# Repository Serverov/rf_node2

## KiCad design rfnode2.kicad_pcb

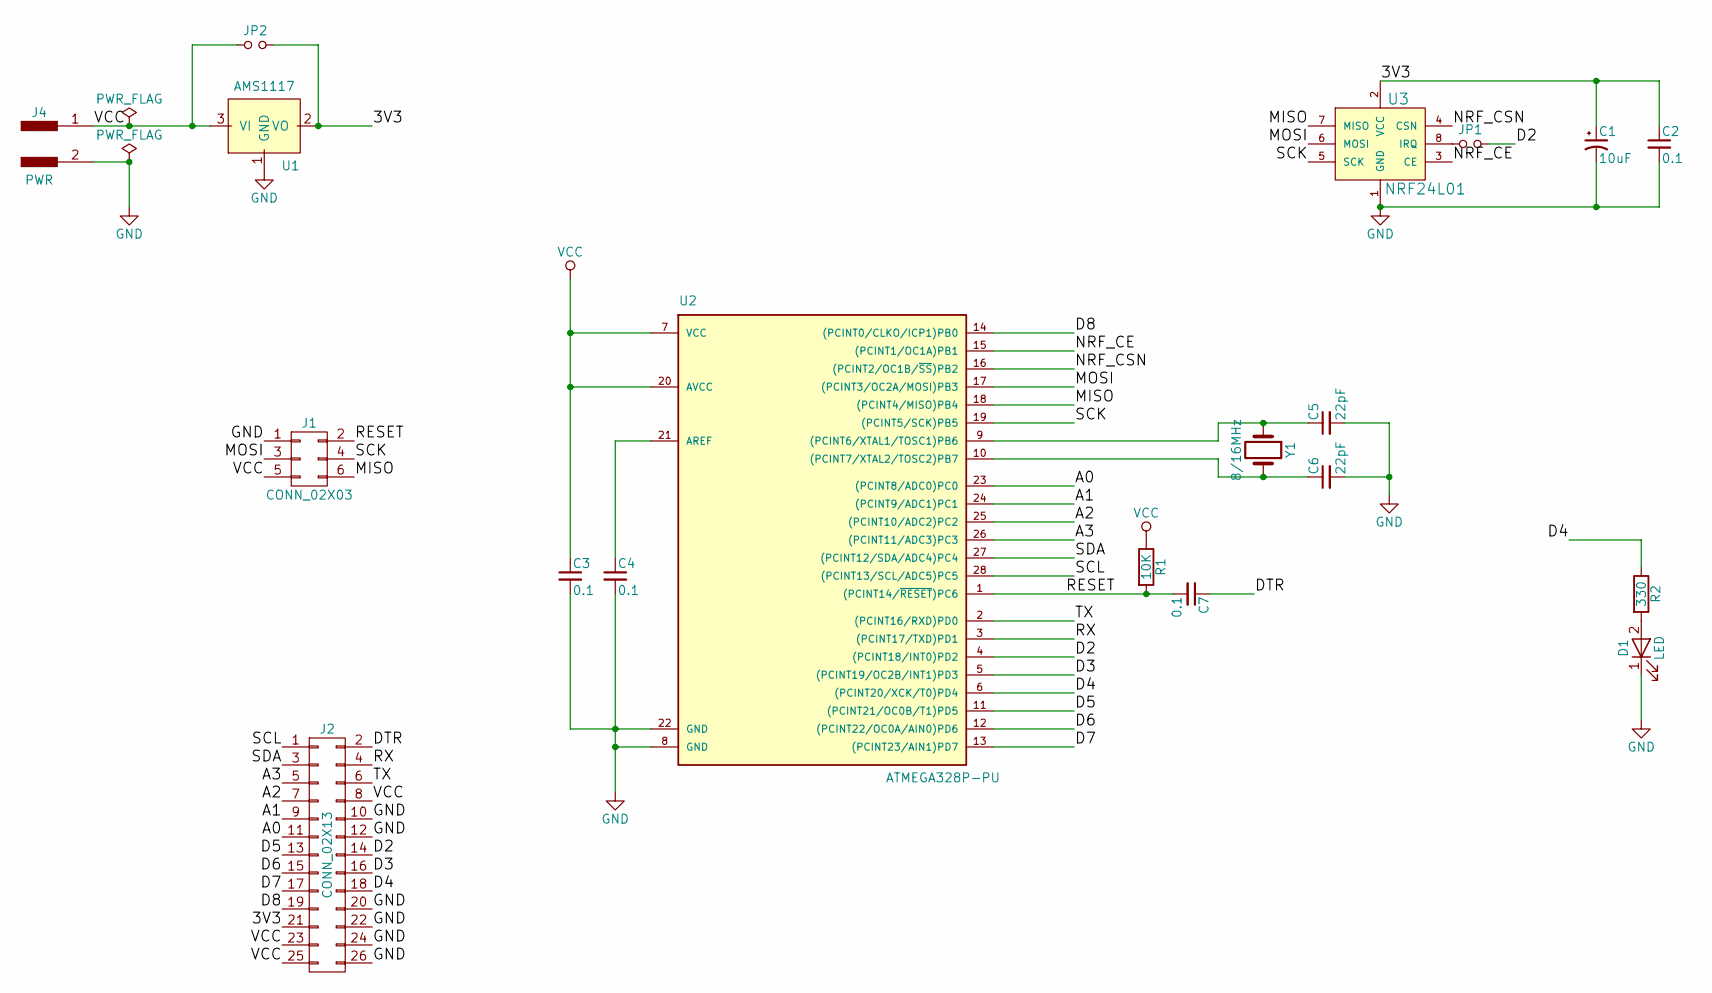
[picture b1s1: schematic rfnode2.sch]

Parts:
C1: 10uF; CP_Radial_D5.0mm_P2.00mm
C2, C3, C4, C7: 0.1; C_0805_HandSoldering
C5, C6: 22pF; C_0805_HandSoldering
D1: LED; LED_D3.0mm
J1: CONN_02X03; Pin_Header_Straight_2x03_Pitch2.54mm
J2: CONN_02X13; Pin_Header_Straight_2x13_Pitch2.54mm
J4: PWR; Pin_Header_Straight_1x02_Pitch2.54mm
JP1: IRQ; S_JUMPER_2
JP2: 3V3; S_JUMPER_2
R1: 10K; R_0805_HandSoldering
R2: 330; R_0805_HandSoldering
U1: AMS1117; SOT-223
U2: ATMEGA328P-PU; DIP-28_W7.62mm_Socket
U3: NRF24L01
Y1: 8/16MHz; Resonator-2pin_w10.0mm_h5.0mm

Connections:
/3V3: C1.1, C2.1, J2.21, JP2.2, U1.2 (VO), U3.2 (VCC)
/A0: J2.11, U2.23 ((PCINT8/ADC0)PC0)
/A1: J2.9, U2.24 ((PCINT9/ADC1)PC1)
/A2: J2.7, U2.25 ((PCINT10/ADC2)PC2)
/A3: J2.5, U2.26 ((PCINT11/ADC3)PC3)
/D2: J2.14, JP1.2, U2.4 ((PCINT18/INT0)PD2)
/D3: J2.16, U2.5 ((PCINT19/OC2B/INT1)PD3)
/D4: J2.18, R2.1, U2.6 ((PCINT20/XCK/T0)PD4)
/D5: J2.13, U2.11 ((PCINT21/OC0B/T1)PD5)
/D6: J2.15, U2.12 ((PCINT22/OC0A/AIN0)PD6)
/D7: J2.17, U2.13 ((PCINT23/AIN1)PD7)
/D8: J2.19, U2.14 ((PCINT0/CLKO/ICP1)PB0)
/DTR: C7.1, J2.2
/MISO: J1.6, U2.18 ((PCINT4/MISO)PB4), U3.7 (MISO)
/MOSI: J1.3, U2.17 ((PCINT3/OC2A/MOSI)PB3), U3.6 (MOSI)
/NRF_CE: U2.15 ((PCINT1/OC1A)PB1), U3.3 (CE)
/NRF_CSN: U2.16 ((PCINT2/OC1B/~SS~)PB2), U3.4 (CSN)
/RESET: C7.2, J1.2, R1.2, U2.1 ((PCINT14/~RESET~)PC6)
/RX: J2.4, U2.3 ((PCINT17/TXD)PD1)
/SCK: J1.4, U2.19 ((PCINT5/SCK)PB5), U3.5 (SCK)
/SCL: J2.1, U2.28 ((PCINT13/SCL/ADC5)PC5)
/SDA: J2.3, U2.27 ((PCINT12/SDA/ADC4)PC4)
/TX: J2.6, U2.2 ((PCINT16/RXD)PD0)
GND: C1.2, C2.2, C3.2, C4.2, C5.2, C6.2, D1.1 (K), J1.1, J2.10, J2.12, J2.20, J2.22, J2.24, J2.26, J4.2, U1.1 (GND), U2.8 (GND), U2.22 (GND), U3.1 (GND)
unnamed: C4.1, U2.21 (AREF)
unnamed: C5.1, U2.9 ((PCINT6/XTAL1/TOSC1)PB6), Y1.1
unnamed: C6.1, U2.10 ((PCINT7/XTAL2/TOSC2)PB7), Y1.2
unnamed: D1.2 (A), R2.2
unnamed: JP1.1, U3.8 (IRQ)
VCC: C3.1, J1.5, J2.8, J2.23, J2.25, J4.1, JP2.1, R1.1, U1.3 (VI), U2.7 (VCC), U2.20 (AVCC)

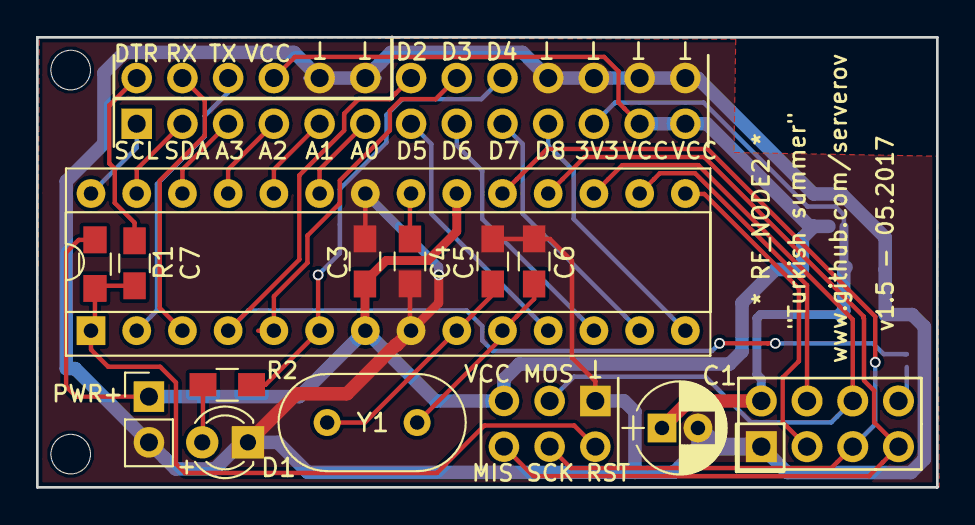
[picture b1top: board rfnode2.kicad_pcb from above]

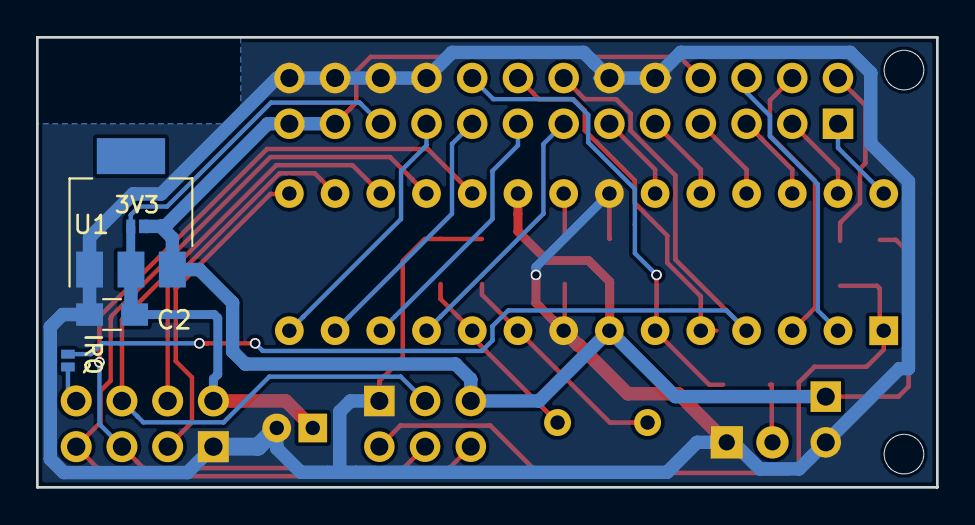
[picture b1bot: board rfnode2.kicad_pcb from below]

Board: 2 copper layers, 50.0 x 25.0 mm, 21 parts (4 on the bottom side), 30 nets.

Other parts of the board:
Hole1, Hole2: MountingHole_2.2mm_M2
